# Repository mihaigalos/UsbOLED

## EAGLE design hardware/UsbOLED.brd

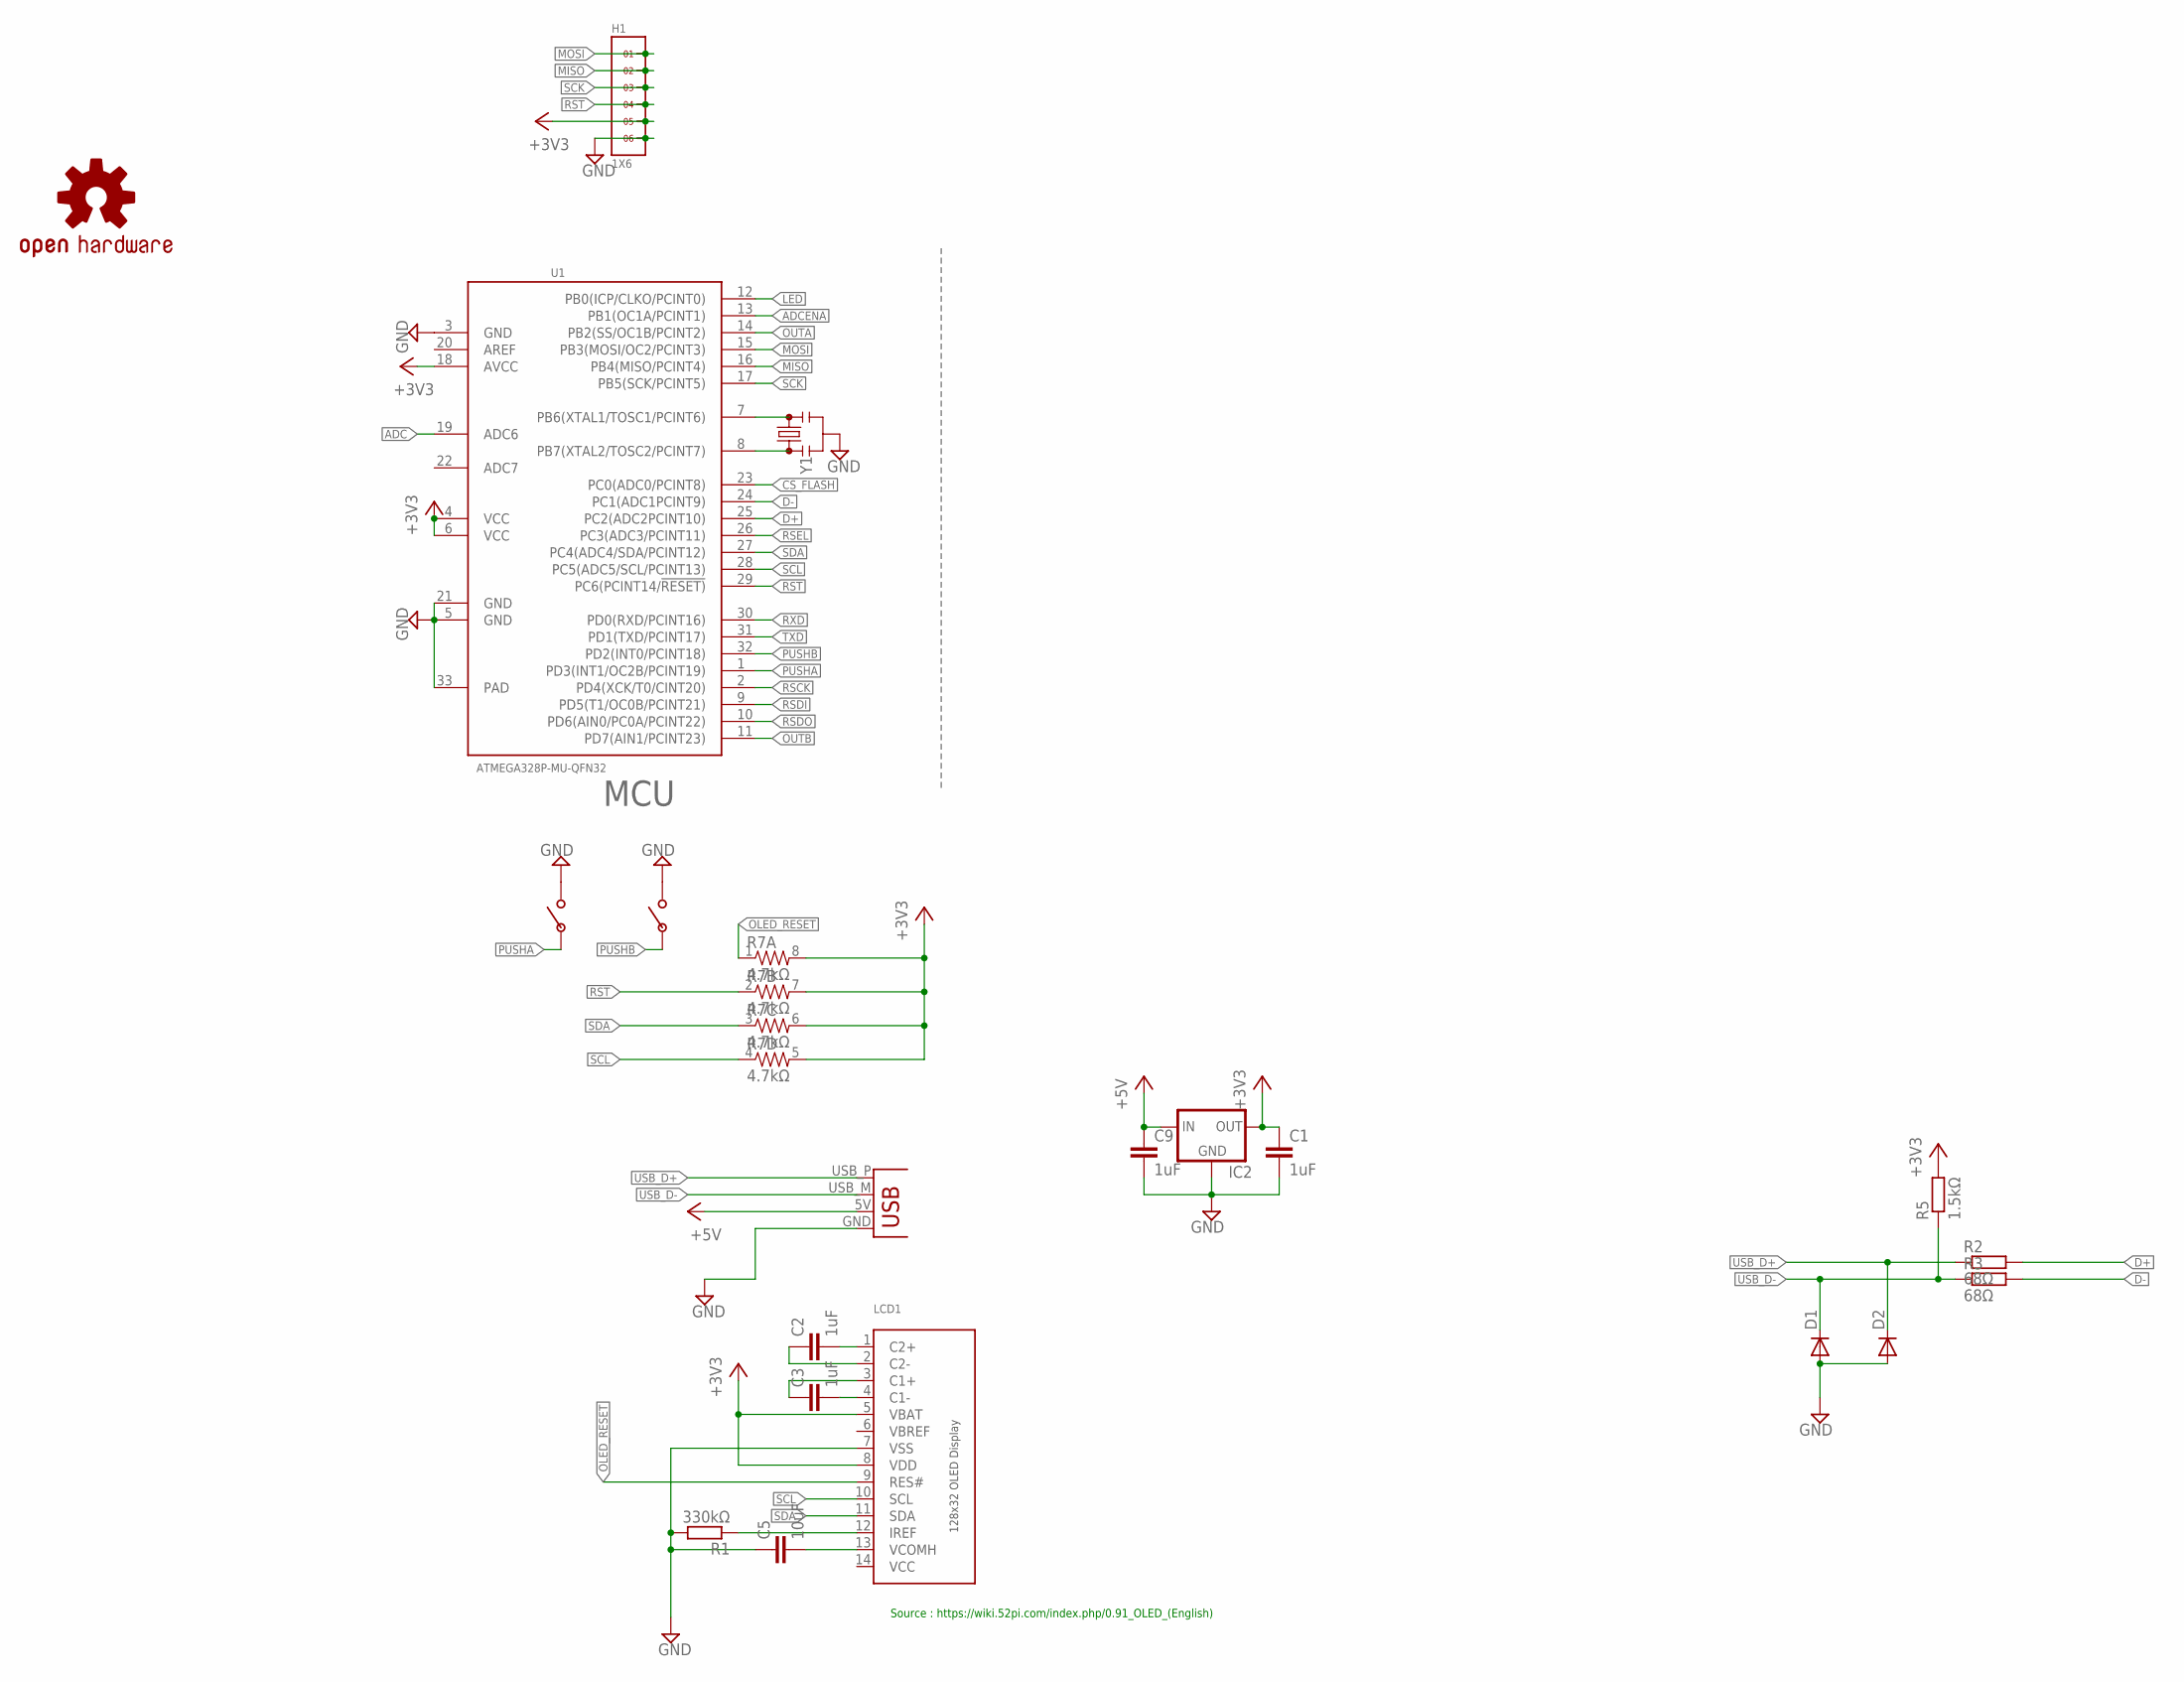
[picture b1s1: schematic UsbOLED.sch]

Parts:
C1, C2, C3, C9: 1uF; C0603
C5: 10uF; C0603
D1, D2: DIODE-SOD523; SOD523
H1: 1X6
IC2: MCP1700TT; SOT-23
LCD1: DISP_OLED_UG-2832HSWEG02; UG-2832HSWEG02_WRAPUNDER
LOGO1: OSHW-LOGOS; OSHW-LOGO-S
R1: 330kΩ; R0603
R2, R3: 68Ω; R0603
R5: 1.5kΩ; R0603
R7: 4.7kΩ; 0603-ARV
U1: ATMEGA328P-MU-QFN32; QFN32G-0.5-5X5MM
U$1, U$3: PUSHBUTTON_4X2.5
X1: USBPCB; USB-A-PCB
Y1: RESONATORSMD-3.2X1.3; RESONATOR-SMD-3.2X1.3

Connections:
+3V3: C1.1, H1.5, IC2.2 (OUT), LCD1.5 (VBAT), LCD1.8 (VDD), R5.2, R7.5 (2), R7.6 (2), R7.7 (2), R7.8 (2), U1.4 (VCC), U1.6 (VCC), U1.18 (AVCC)
+5V: C9.1, IC2.3 (IN), X1.5V (VBUS)
ADC: U1.19 (ADC6)
ADCENA: U1.13 (PB1(OC1A/PCINT1))
CS_FLASH: U1.23 (PC0(ADC0/PCINT8))
D+: R2.2, U1.25 (PC2(ADC2PCINT10))
D-: R3.2, U1.24 (PC1(ADC1PCINT9))
GND: C1.2, C5.1, C9.2, D1.A, D2.A, H1.6, IC2.1 (GND), LCD1.7 (VSS), R1.2, U1.3 (GND), U1.5 (GND), U1.21 (GND), U1.33 (PAD), U$1.P$2, U$3.P$2, X1.GND, Y1.2
LED: U1.12 (PB0(ICP/CLKO/PCINT0))
MISO: H1.2, U1.16 (PB4(MISO/PCINT4))
MOSI: H1.1, U1.15 (PB3(MOSI/OC2/PCINT3))
unnamed: C2.2, LCD1.1 (C2+)
unnamed: C2.1, LCD1.2 (C2-)
unnamed: C3.2, LCD1.4 (C1-)
unnamed: C3.1, LCD1.3 (C1+)
unnamed: LCD1.12 (IREF), R1.1
unnamed: U1.7 (PB6(XTAL1/TOSC1/PCINT6)), Y1.3
unnamed: C5.2, LCD1.13 (VCOMH)
unnamed: U1.8 (PB7(XTAL2/TOSC2/PCINT7)), Y1.1
OLED_RESET: LCD1.9 (RES#), R7.1
OUTA: U1.14 (PB2(SS/OC1B/PCINT2))
OUTB: U1.11 (PD7(AIN1/PCINT23))
PUSHA: U1.1 (PD3(INT1/OC2B/PCINT19)), U$1.P$1
PUSHB: U1.32 (PD2(INT0/PCINT18)), U$3.P$1
RSCK: U1.2 (PD4(XCK/T0/CINT20))
RSDI: U1.9 (PD5(T1/OC0B/PCINT21))
RSDO: U1.10 (PD6(AIN0/PC0A/PCINT22))
RSEL: U1.26 (PC3(ADC3/PCINT11))
RST: H1.4, R7.2 (1), U1.29 (PC6(PCINT14/!RESET))
RXD: U1.30 (PD0(RXD/PCINT16))
SCK: H1.3, U1.17 (PB5(SCK/PCINT5))
SCL: LCD1.10 (SCL), R7.4 (1), U1.28 (PC5(ADC5/SCL/PCINT13))
SDA: LCD1.11 (SDA), R7.3 (1), U1.27 (PC4(ADC4/SDA/PCINT12))
TXD: U1.31 (PD1(TXD/PCINT17))
USB_D+: D2.C, R2.1, X1.USB_P (D+)
USB_D-: D1.C, R3.1, R5.1, X1.USB_M (D-)
VBREF: LCD1.6 (VBREF)
VCC: LCD1.14 (VCC)

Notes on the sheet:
MCU
Source : https://wiki.52pi.com/index.php/0.91_OLED_(English)

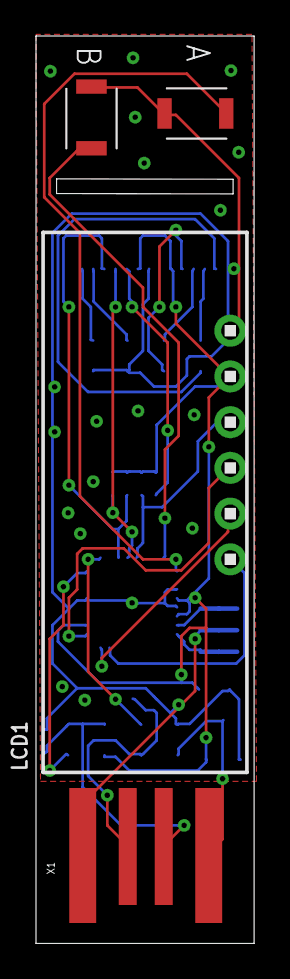
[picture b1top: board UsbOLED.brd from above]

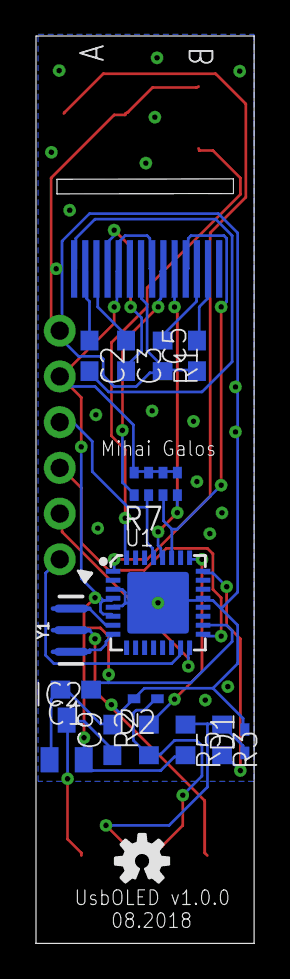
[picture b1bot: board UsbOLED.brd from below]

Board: 2 copper layers, 12.1 x 50.4 mm, 21 parts (16 on the bottom side), 24 nets.

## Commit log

2018-07-04 Initial routing
2018-07-04 urther refine
2018-07-04 Improve routing, add version
2018-07-04 Add pushbuttons A,B
2018-07-04 Improve GND

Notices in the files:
parts and their libraries:
SparkFun: Licensing: CC v3.0 Share-Alike You are welcome to use this library for commercial purposes.
SparkFun-Clocks: Licensing: Creative Commons ShareAlike 4.0 International - https://creativecommons.org/licenses/by-sa/4.0
